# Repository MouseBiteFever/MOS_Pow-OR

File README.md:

MOS Pow-OR
======

MOSFET based Power multiplexer

This will be a repository for the Eagle CAD design files of the MOS Pow-OR power multiplexer board.
<br>To follow development of the board please go to http://MouseBiteFever.tumblr.com
<br><br>

<br />This work is licensed under a <a rel="license" href="http://creativecommons.org/licenses/by-sa/4.0/">Creative Commons Attribution-ShareAlike 4.0 International License</a>.

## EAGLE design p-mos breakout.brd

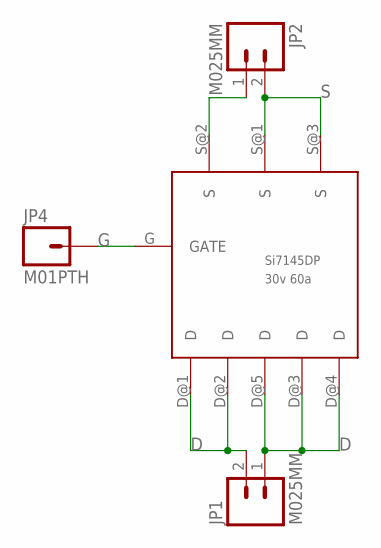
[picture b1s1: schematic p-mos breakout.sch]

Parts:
JP1, JP2: M025MM; SCREWTERMINAL-5MM-2
JP4: M01PTH; 1X01
U$1: PMOS-SI7145DP; S0-8

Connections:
D: JP1.1, JP1.2, U$1.D@1 (D), U$1.D@2 (D), U$1.D@3 (D), U$1.D@4 (D), U$1.D@5 (D)
G: JP4.1, U$1.G (GATE)
S: JP2.1, JP2.2, U$1.S@1 (S), U$1.S@2 (S), U$1.S@3 (S)

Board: 2 copper layers, 4 parts (0 on the bottom side), 3 nets, no tracks yet.

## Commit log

2014-05-18 Readme
    Basic files to open repo
2014-05-19 P-Mos breakout
    Adding board files and image of Breakout Board for P-Mos

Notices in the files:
parts and their libraries:
SparkFun-Connectors: Licensing: CC v3.0 Share-Alike You are welcome to use this library for commercial purposes.
